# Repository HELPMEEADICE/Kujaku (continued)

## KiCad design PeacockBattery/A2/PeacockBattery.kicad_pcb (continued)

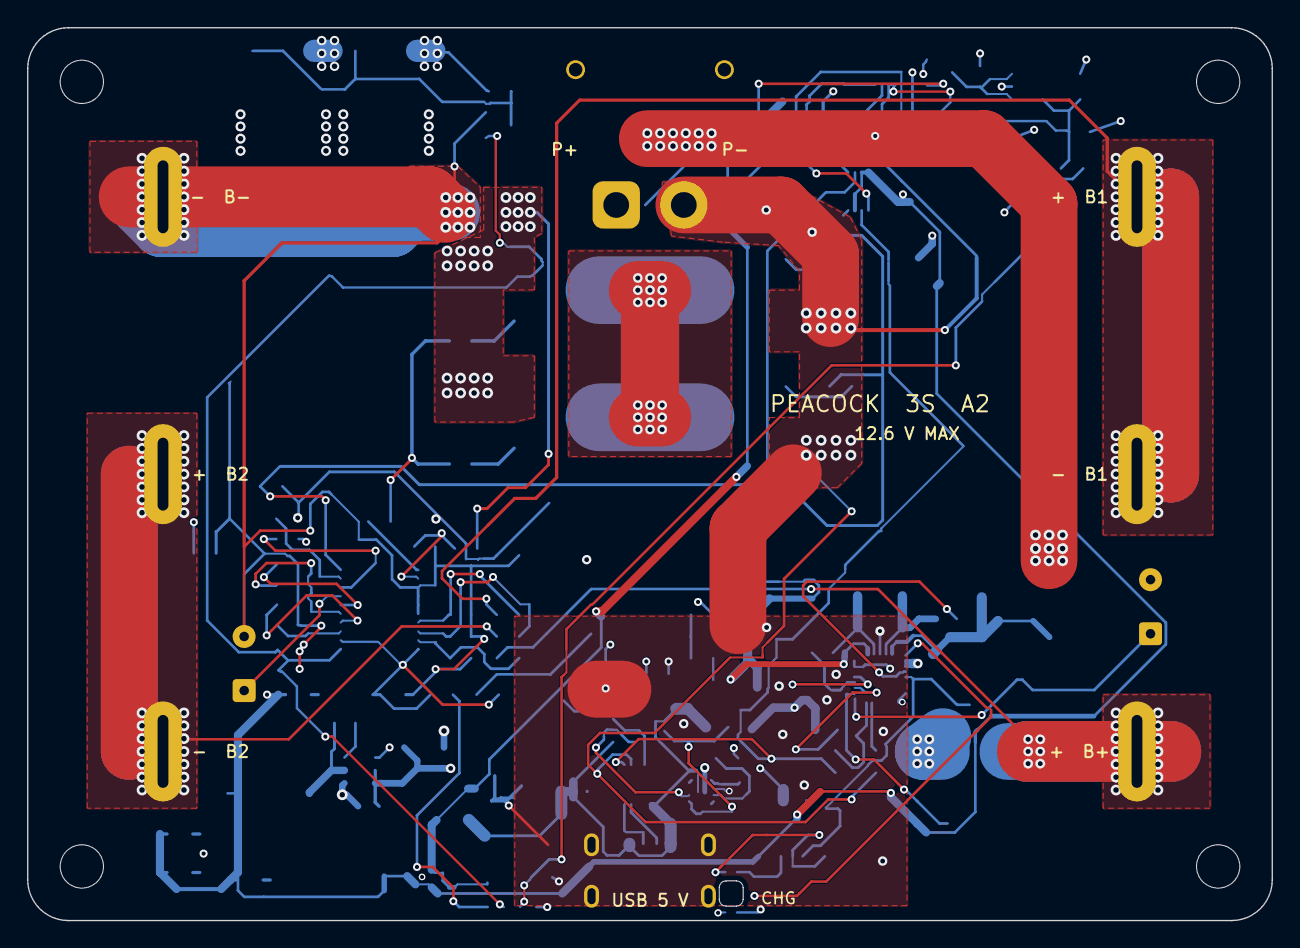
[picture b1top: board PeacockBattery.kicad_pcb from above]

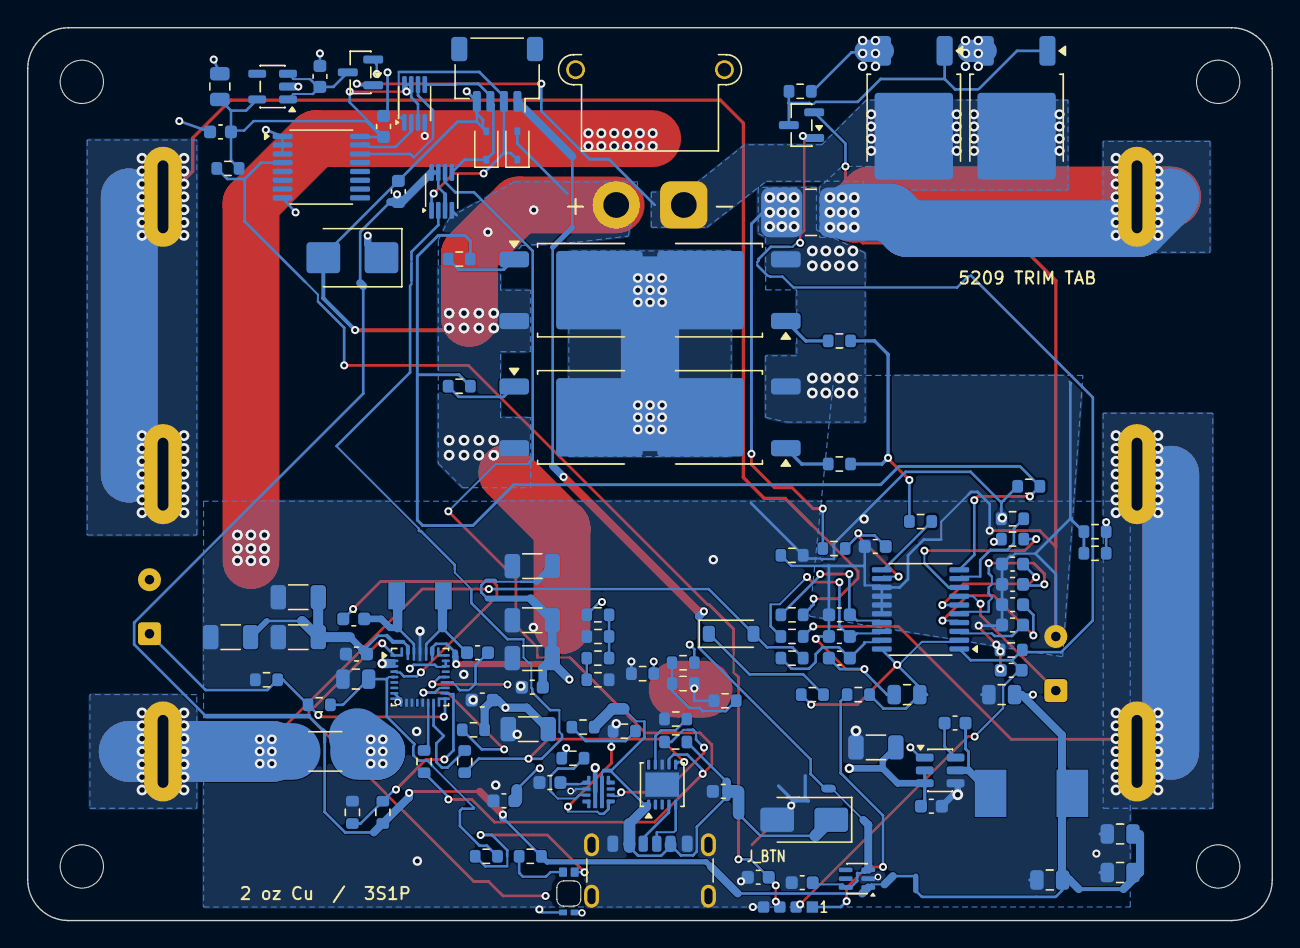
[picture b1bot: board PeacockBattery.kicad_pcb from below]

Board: 4 copper layers, 92.0 x 66.0 mm, 126 parts (116 on the bottom side), 75 nets.

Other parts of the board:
MH1, MH2, MH3, MH4: MountingHole_3.2mm_M3

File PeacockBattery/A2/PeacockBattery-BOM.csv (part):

位号,数量,规格,厂商,订购型号或规格,KiCad 封装,安装面,LCSC,SMT_Populate,JLCPCB 库别,装配说明
BT1,1,5209 trimmed,Keystone,TBD,PeacockBattery:Keystone_5209_Trimmed,F,,No,N/A,焊接前修剪原装长焊耳，装入镀通槽并完全坐靠后从 PCB 底面量取突出 ≤1.50 mm。名义肩下 2.80 ±0.10 mm。去毛刺并复核插入与焊脚。
BT2,1,5209 trimmed,Keystone,TBD,PeacockBattery:Keystone_5209_Trimmed,F,,No,N/A,焊接前修剪原装长焊耳，装入镀通槽并完全坐靠后从 PCB 底面量取突出 ≤1.50 mm。名义肩下 2.80 ±0.10 mm。去毛刺并复核插入与焊脚。
BT3,1,5209 trimmed,Keystone,TBD,PeacockBattery:Keystone_5209_Trimmed,F,,No,N/A,焊接前修剪原装长焊耳，装入镀通槽并完全坐靠后从 PCB 底面量取突出 ≤1.50 mm。名义肩下 2.80 ±0.10 mm。去毛刺并复核插入与焊脚。
BT4,1,5209 trimmed,Keystone,TBD,PeacockBattery:Keystone_5209_Trimmed,F,,No,N/A,焊接前修剪原装长焊耳，装入镀通槽并完全坐靠后从 PCB 底面量取突出 ≤1.50 mm。名义肩下 2.80 ±0.10 mm。去毛刺并复核插入与焊脚。
BT5,1,5209 trimmed,Keystone,TBD,PeacockBattery:Keystone_5209_Trimmed,F,,No,N/A,焊接前修剪原装长焊耳，装入镀通槽并完全坐靠后从 PCB 底面量取突出 ≤1.50 mm。名义肩下 2.80 ±0.10 mm。去毛刺并复核插入与焊脚。
BT6,1,5209 trimmed,Keystone,TBD,PeacockBattery:Keystone_5209_Trimmed,F,,No,N/A,焊接前修剪原装长焊耳，装入镀通槽并完全坐靠后从 PCB 底面量取突出 ≤1.50 mm。名义肩下 2.80 ±0.10 mm。去毛刺并复核插入与焊脚。
C1,1,100nF 50V,YAGEO,CC0603KRX7R9BB104,Capacitor_SMD:C_0603_1608Metric,B,C14663,Yes,Basic,X7R，±10%，未标耐压者用 ≥50 V，复核直流偏压
C2,1,100nF 50V,YAGEO,CC0603KRX7R9BB104,Capacitor_SMD:C_0603_1608Metric,B,C14663,Yes,Basic,X7R，±10%，未标耐压者用 ≥50 V，复核直流偏压
C3,1,100nF 50V,YAGEO,CC0603KRX7R9BB104,Capacitor_SMD:C_0603_1608Metric,B,C14663,Yes,Basic,X7R，±10%，未标耐压者用 ≥50 V，复核直流偏压
C4,1,10uF 25V,Samsung Electro Mechanics,CL21A106KAYNNNE,Capacitor_SMD:C_0805_2012Metric,B,C15850,Yes,Basic,BMS VCC 储能，10 µF / 25 V，0805。
C5,1,100nF 50V,YAGEO,CC0603KRX7R9BB104,Capacitor_SMD:C_0603_1608Metric,B,C14663,Yes,Basic,X7R，±10%，未标耐压者用 ≥50 V，复核直流偏压
C6,1,100nF 50V,YAGEO,CC0603KRX7R9BB104,Capacitor_SMD:C_0603_1608Metric,B,C14663,Yes,Basic,X7R，±10%，未标耐压者用 ≥50 V，复核直流偏压
C7,1,10nF 50V,FH Guangdong Fenghua Advanced Tech,0603B103K500NT,Capacitor_SMD:C_0603_1608Metric,B,C57112,Yes,Basic,过流定时，保持 10 nF / 50 V。
C8,1,10nF 50V,FH Guangdong Fenghua Advanced Tech,0603B103K500NT,Capacitor_SMD:C_0603_1608Metric,B,C57112,Yes,Basic,过流定时，保持 10 nF / 50 V。
C9,1,10nF 50V,FH Guangdong Fenghua Advanced Tech,0603B103K500NT,Capacitor_SMD:C_0603_1608Metric,B,C57112,Yes,Basic,分流检测滤波，保持 10 nF / 50 V。
C10,1,1uF 50V,Samsung Electro Mechanics,CL10A105KB8NNNC,Capacitor_SMD:C_0603_1608Metric,B,C15849,Yes,Basic,陶瓷 X7R 或 X5R。按偏压下有效容量、纹波电流和公差选型。
C11,1,4.7nF 50V,FH Guangdong Fenghua Advanced Tech,0603B472K500NT,Capacitor_SMD:C_0603_1608Metric,B,C53987,Yes,Basic,电子保险丝 dV/dt 电容，保持 4.7 nF。
C12,1,1uF 50V,Samsung Electro Mechanics,CL10A105KB8NNNC,Capacitor_SMD:C_0603_1608Metric,B,C15849,Yes,Basic,陶瓷 X7R 或 X5R。按偏压下有效容量、纹波电流和公差选型。
C13,1,4.7uF 25V,Samsung Electro Mechanics,CL21A475KAQNNNE,Capacitor_SMD:C_0805_2012Metric,B,C1779,Yes,Basic,REGN 去耦，4.7 µF / 25 V。
C14,1,100nF 50V,YAGEO,CC0603KRX7R9BB104,Capacitor_SMD:C_0603_1608Metric,B,C14663,Yes,Basic,陶瓷 X7R 或 X5R。按偏压下有效容量、纹波电流和公差选型。
C15,1,100nF 50V,YAGEO,CC0603KRX7R9BB104,Capacitor_SMD:C_0603_1608Metric,B,C14663,Yes,Basic,陶瓷 X7R 或 X5R。按偏压下有效容量、纹波电流和公差选型。
C16,1,10uF 50V,Samsung Electro Mechanics,CL31A106KBHNNNE,Capacitor_SMD:C_1206_3216Metric,B,C13585,Yes,Basic,10 µF / 50 V、1206，保留受偏压下的容量余量。
C17,1,10uF 50V,Samsung Electro Mechanics,CL31A106KBHNNNE,Capacitor_SMD:C_1206_3216Metric,B,C13585,Yes,Basic,10 µF / 50 V、1206，保留受偏压下的容量余量。
C18,1,10uF 50V,Samsung Electro Mechanics,CL31A106KBHNNNE,Capacitor_SMD:C_1206_3216Metric,B,C13585,Yes,Basic,10 µF / 50 V、1206，保留受偏压下的容量余量。
C19,1,100nF 50V,YAGEO,CC0603KRX7R9BB104,Capacitor_SMD:C_0603_1608Metric,B,C14663,Yes,Basic,陶瓷 X7R 或 X5R。按偏压下有效容量、纹波电流和公差选型。
C20,1,22uF 25V,Samsung Electro Mechanics,CL31A226KAHNNNE,Capacitor_SMD:C_1206_3216Metric,B,C12891,Yes,Basic,22 µF / 25 V、1206，保留充电 SYS 在偏压下的容量余量。
C21,1,22uF 25V,Samsung Electro Mechanics,CL31A226KAHNNNE,Capacitor_SMD:C_1206_3216Metric,B,C12891,Yes,Basic,22 µF / 25 V、1206，保留充电 SYS 在偏压下的容量余量。
C22,1,22uF 25V,Samsung Electro Mechanics,CL31A226KAHNNNE,Capacitor_SMD:C_1206_3216Metric,B,C12891,Yes,Basic,22 µF / 25 V、1206，保留充电 SYS 在偏压下的容量余量。
C23,1,100nF 50V,YAGEO,CC0603KRX7R9BB104,Capacitor_SMD:C_0603_1608Metric,B,C14663,Yes,Basic,陶瓷 X7R 或 X5R。按偏压下有效容量、纹波电流和公差选型。
C24,1,10uF 50V,Samsung Electro Mechanics,CL31A106KBHNNNE,Capacitor_SMD:C_1206_3216Metric,B,C13585,Yes,Basic,10 µF / 50 V、1206，保留受偏压下的容量余量。
C25,1,100nF 50V,YAGEO,CC0603KRX7R9BB104,Capacitor_SMD:C_0603_1608Metric,B,C14663,Yes,Basic,陶瓷 X7R 或 X5R。按偏压下有效容量、纹波电流和公差选型。
C26,1,10uF 50V,Samsung Electro Mechanics,CL31A106KBHNNNE,Capacitor_SMD:C_1206_3216Metric,B,C13585,Yes,Basic,AP63205 输入储能，50 V 器件，临近 VIN。
C27,1,100nF 50V,YAGEO,CC0603KRX7R9BB104,Capacitor_SMD:C_0603_1608Metric,B,C14663,Yes,Basic,AP63205 VIN 与 GND 的近端高频旁路。
C29,1,100nF 50V,YAGEO,CC0603KRX7R9BB104,Capacitor_SMD:C_0603_1608Metric,B,C14663,Yes,Basic,陶瓷 X7R 或 X5R。按偏压下有效容量、纹波电流和公差选型。
C30,1,22uF 25V,Samsung Electro Mechanics,CL21A226MAQNNNE,Capacitor_SMD:C_0805_2012Metric,B,C45783,Yes,Basic,22 µF / 25 V、0805，WAKE_5V 输出电容。
C31,1,22uF 25V,Samsung Electro Mechanics,CL21A226MAQNNNE,Capacitor_SMD:C_0805_2012Metric,B,C45783,Yes,Basic,22 µF / 25 V、0805，WAKE_5V 输出电容。
C32,1,22uF 25V,Samsung Electro Mechanics,CL21A226MAQNNNE,Capacitor_SMD:C_0805_2012Metric,B,C45783,Yes,Basic,22 µF / 25 V、0805，WAKE_5V 输出电容。
C33,1,22uF 25V,Samsung Electro Mechanics,CL21A226MAQNNNE,Capacitor_SMD:C_0805_2012Metric,B,C45783,Yes,Basic,22 µF / 25 V、0805，WAKE_5V 输出电容。
C34,1,1uF 50V,Samsung Electro Mechanics,CL10A105KB8NNNC,Capacitor_SMD:C_0603_1608Metric,B,C15849,Yes,Basic,陶瓷 X7R 或 X5R。按偏压下有效容量、纹波电流和公差选型。
C35,1,100nF 50V,YAGEO,CC0603KRX7R9BB104,Capacitor_SMD:C_0603_1608Metric,B,C14663,Yes,Basic,陶瓷 X7R 或 X5R。按偏压下有效容量、纹波电流和公差选型。
C36,1,100nF 50V,YAGEO,CC0603KRX7R9BB104,Capacitor_SMD:C_0603_1608Metric,B,C14663,Yes,Basic,
C37,1,100nF 50V,YAGEO,CC0603KRX7R9BB104,Capacitor_SMD:C_0603_1608Metric,B,C14663,Yes,Basic,
C38,1,1uF 50V,Samsung,CL10A105KB8NNNC,Capacitor_SMD:C_0603_1608Metric,B,C15849,Yes,Basic,
C39,1,10uF 25V,Samsung,CL21A106KAYNNNE,Capacitor_SMD:C_0805_2012Metric,B,C15850,Yes,Basic,
C40,1,100nF 50V,YAGEO,CC0603KRX7R9BB104,Capacitor_SMD:C_0603_1608Metric,B,C14663,Yes,Basic,
C41,1,100nF 50V,YAGEO,CC0603KRX7R9BB104,Capacitor_SMD:C_0603_1608Metric,B,C14663,Yes,Basic,
CELL,3,Ø18.50 × 66.50–68.00 mm 凸口 18650,待选,同型号、同批次动力电芯,可拆卸,F,,No,N/A,整组一致性及 15 A 稳态和 20 A 脉冲额定按最终电芯验收。
D1,1,1N4148W,ST Semtech,1N4148W,Diode_SMD:D_SOD-123,B,C81598,Yes,Basic,基础库低漏电高速二极管，SOD-123，1 为阴极。
D2,1,SMBJ15A,hongjiacheng,SMBJ15A,Diode_SMD:D_SMB,B,C19077569,Yes,Preferred Extended,15 V 单向 TVS，SMB，1 为阴极。
D3,1,SMAJ20A,hongjiacheng,SMAJ20A,Diode_SMD:D_SMA,B,C41376408,Yes,Preferred Extended,20 V 单向 TVS，SMA，1 为阴极。热插拔峰值以带线实测为准。
D4,1,23-22B/R7G6C-A30/2T,Everlight Elec,23-22B/R7G6C-A30/2T,PeacockBattery:LED_Everlight_23-22B_Reverse,B,C424084,Yes,Extended,"B 面反向出光，光轴居中于 (52.00, 2.00) mm。1=绿阳，2=绿阴，3=红阳，4=红阴。"
D5,1,PESD3V3U1UA,Nexperia,"PESD3V3U1UA,115",Diode_SMD:D_SOD-323,B,C403915,Yes,Extended,SDA 对地 ESD，1 为阴极。
D6,1,PESD3V3U1UA,Nexperia,"PESD3V3U1UA,115",Diode_SMD:D_SOD-323,B,C403915,Yes,Extended,SCL 对地 ESD，1 为阴极。
D7,1,BAT54C,Jiangsu Changjing Electronics,BAT54C,Package_TO_SOT_SMD:SOT-23,B,C2135,Yes,Extended,XT30_SW 与 WAKE_5V 合路，共阴极。
F1,1,20A / 65V,Littelfuse,0451020.MRL,Fuse:Fuse_Littelfuse-NANO2-451_453,B,C178980,Yes,Extended,20 A 快断保险丝，按装壳温度复核降额
J1,1,USB4125-GF-A,Global Connector Technology,USB4125-GF-A,PeacockBattery:USB4125_HandAssembly,B,C3151650,No,Extended,B 面手焊。不下钢网。六触点双 CC，保留插口中心及 0.80 mm 外伸。
J2,1,XT30PW-M30.G.Y,Changzhou Amass Elec,XT30PW-M30.G.Y,PeacockBattery:XT30PW-M_Edge,B,C431092,No,Extended,B 面手焊。保留 5.00 mm 脚距及原固定孔，1=P+，2=P−。
J3,1,10k BMS sensor,通用,"10k NTC, insulated leads",Connector_Wire:SolderWire-0.15sqmm_1x02_P4mm_D0.5mm_OD1.5mm,B,,No,N/A,需另装电芯贴附式 10 kΩ NTC，温度动作点需标定
J4,1,103AT-2,SEMITEC,103AT-2,Connector_Wire:SolderWire-0.15sqmm_1x02_P4mm_D0.5mm_OD1.5mm,B,,No,N/A,外置绝缘贴附 NTC，10 kΩ / 3435 K，核对接头极性与引脚底面净空。
J5,1,SM04B-SRSS-TB(LF)(SN),JST,SM04B-SRSS-TB(LF)(SN),PeacockBattery:JST_SH_SM04B_HandAssembly,B,C160404,No,Extended,B 面手焊。不下钢网。1=CHG_5V，2=SDA，3=SCL，4=GND。
J6,1,J_BTN,Hand assembly,Wire-to-pad,PeacockBattery:Grip_1x04_SolderPads,B,N/A,No,N/A,J_BTN，四路手焊，B 面无锡膏。红 1、黑 2、黄 3、绿 4。
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
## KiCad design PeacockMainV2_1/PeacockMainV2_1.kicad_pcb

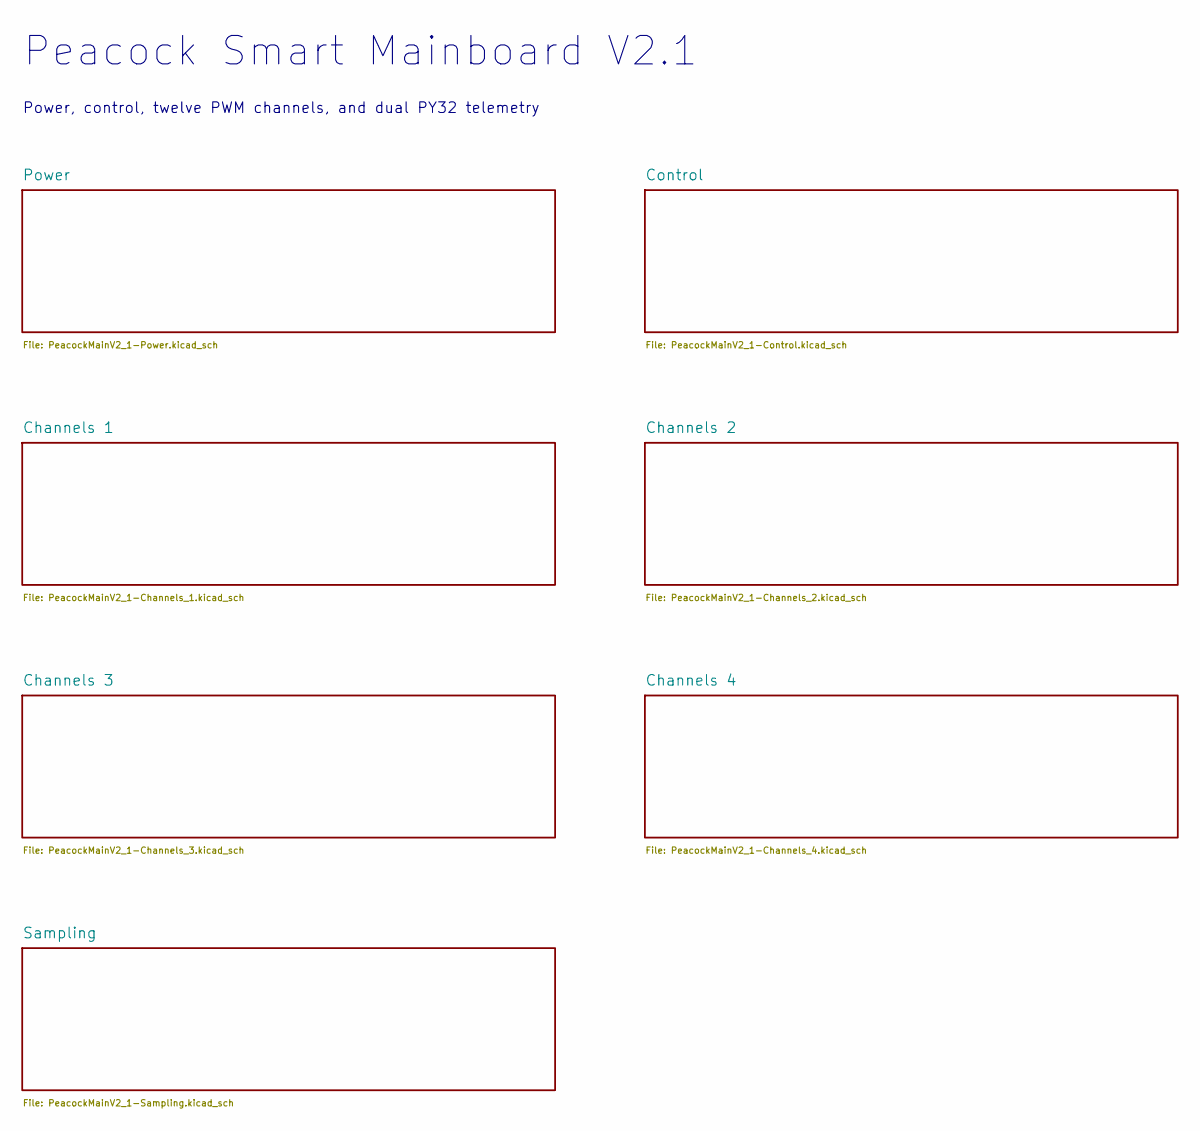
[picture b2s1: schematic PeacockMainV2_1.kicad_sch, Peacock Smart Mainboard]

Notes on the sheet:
Peacock Smart Mainboard V2.1
Power, control, twelve PWM channels, and dual PY32 telemetry

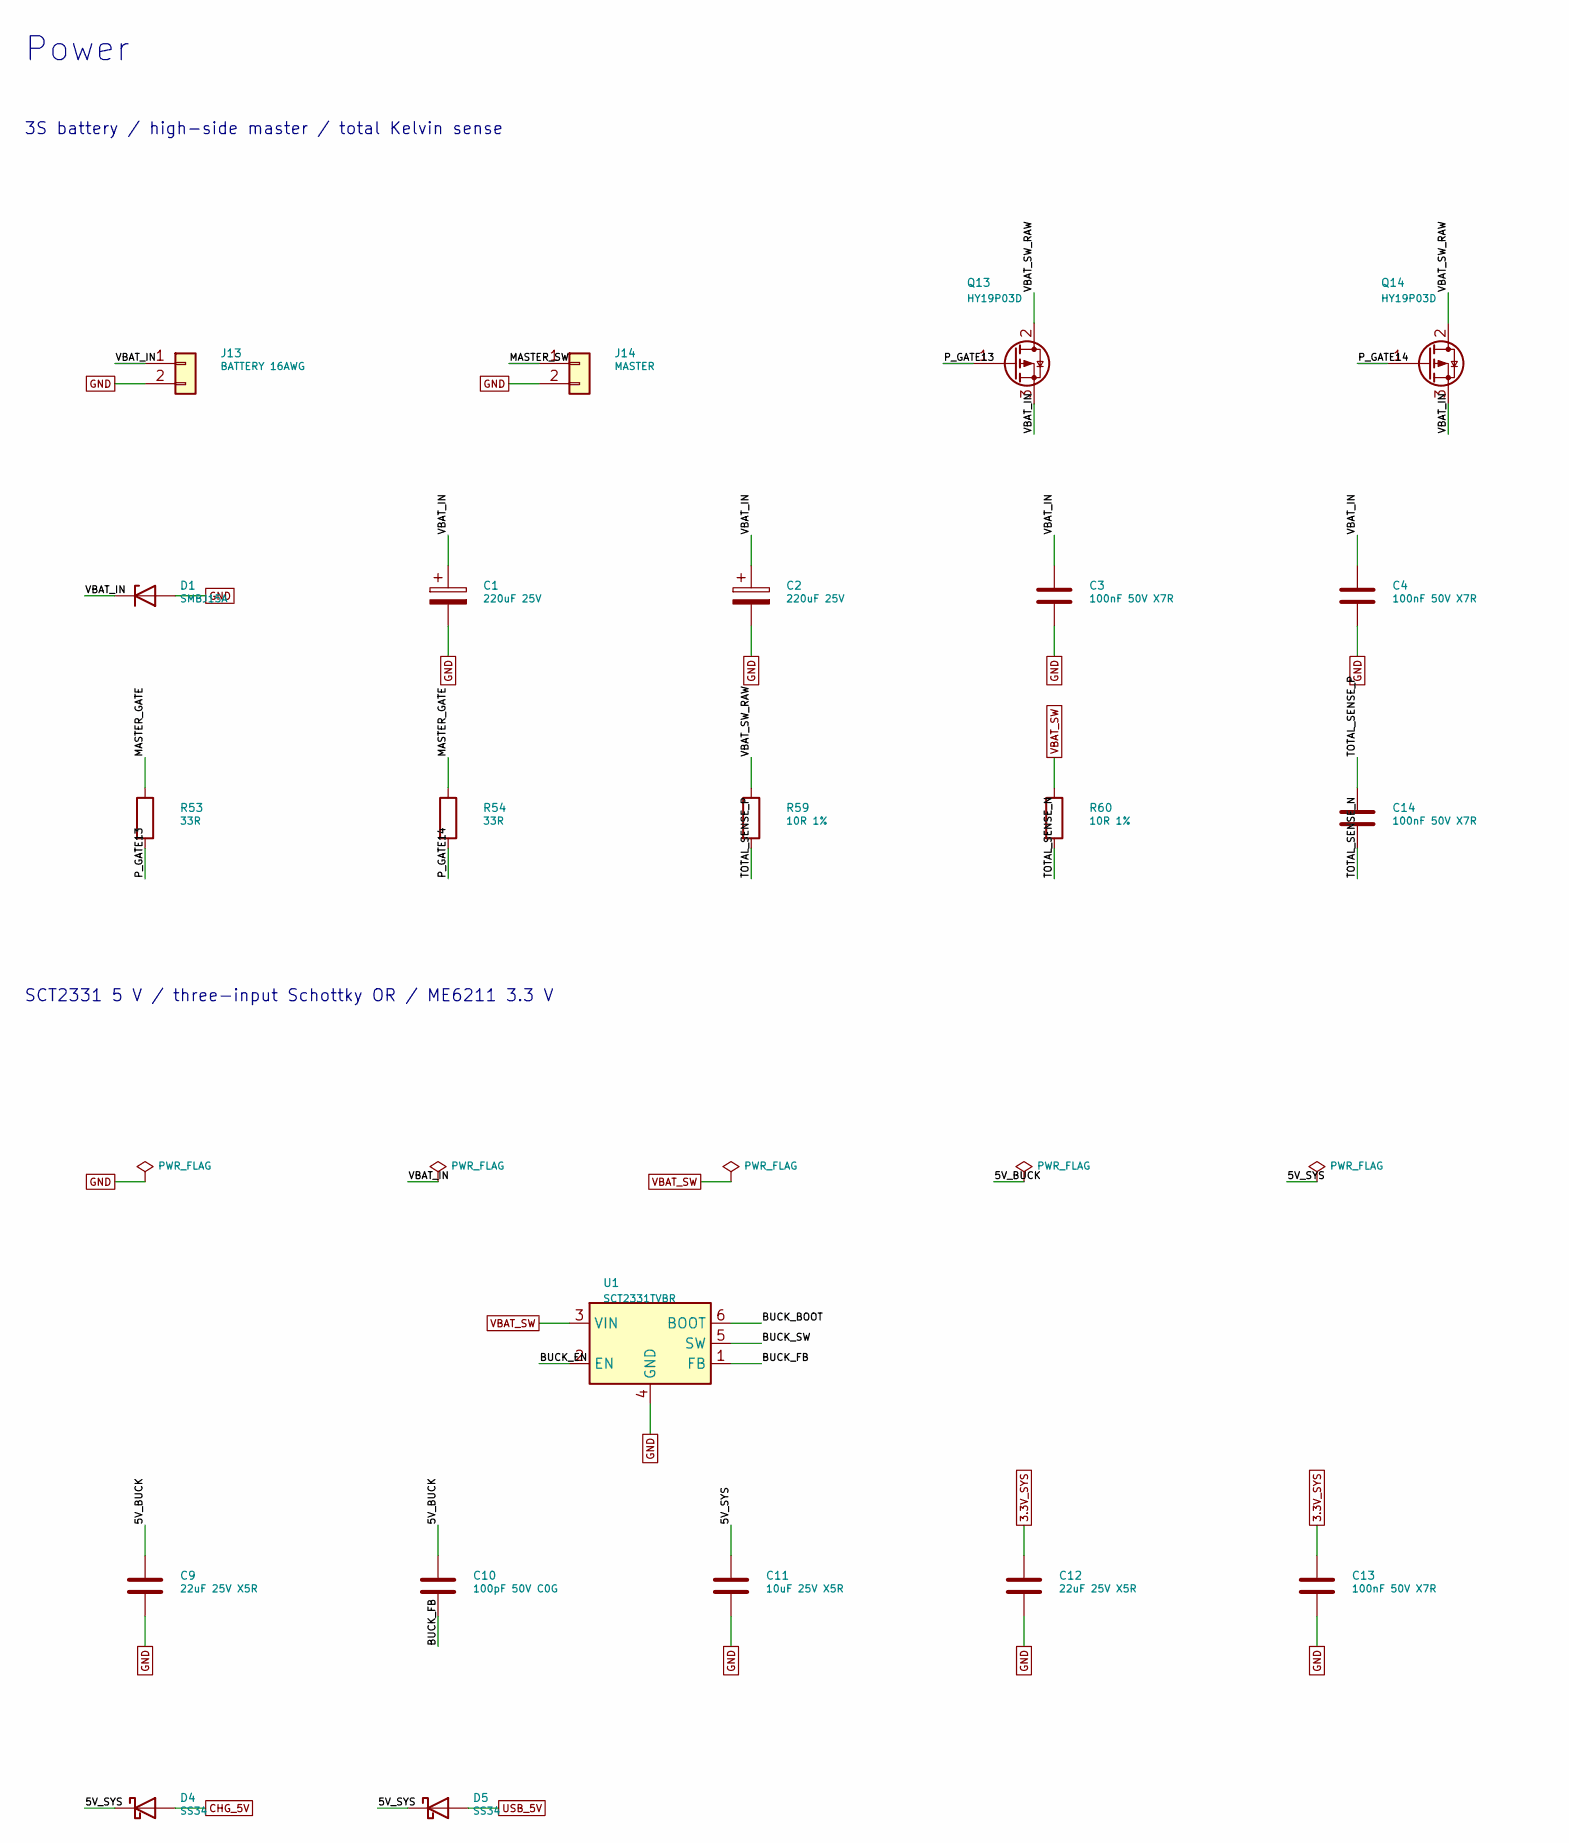
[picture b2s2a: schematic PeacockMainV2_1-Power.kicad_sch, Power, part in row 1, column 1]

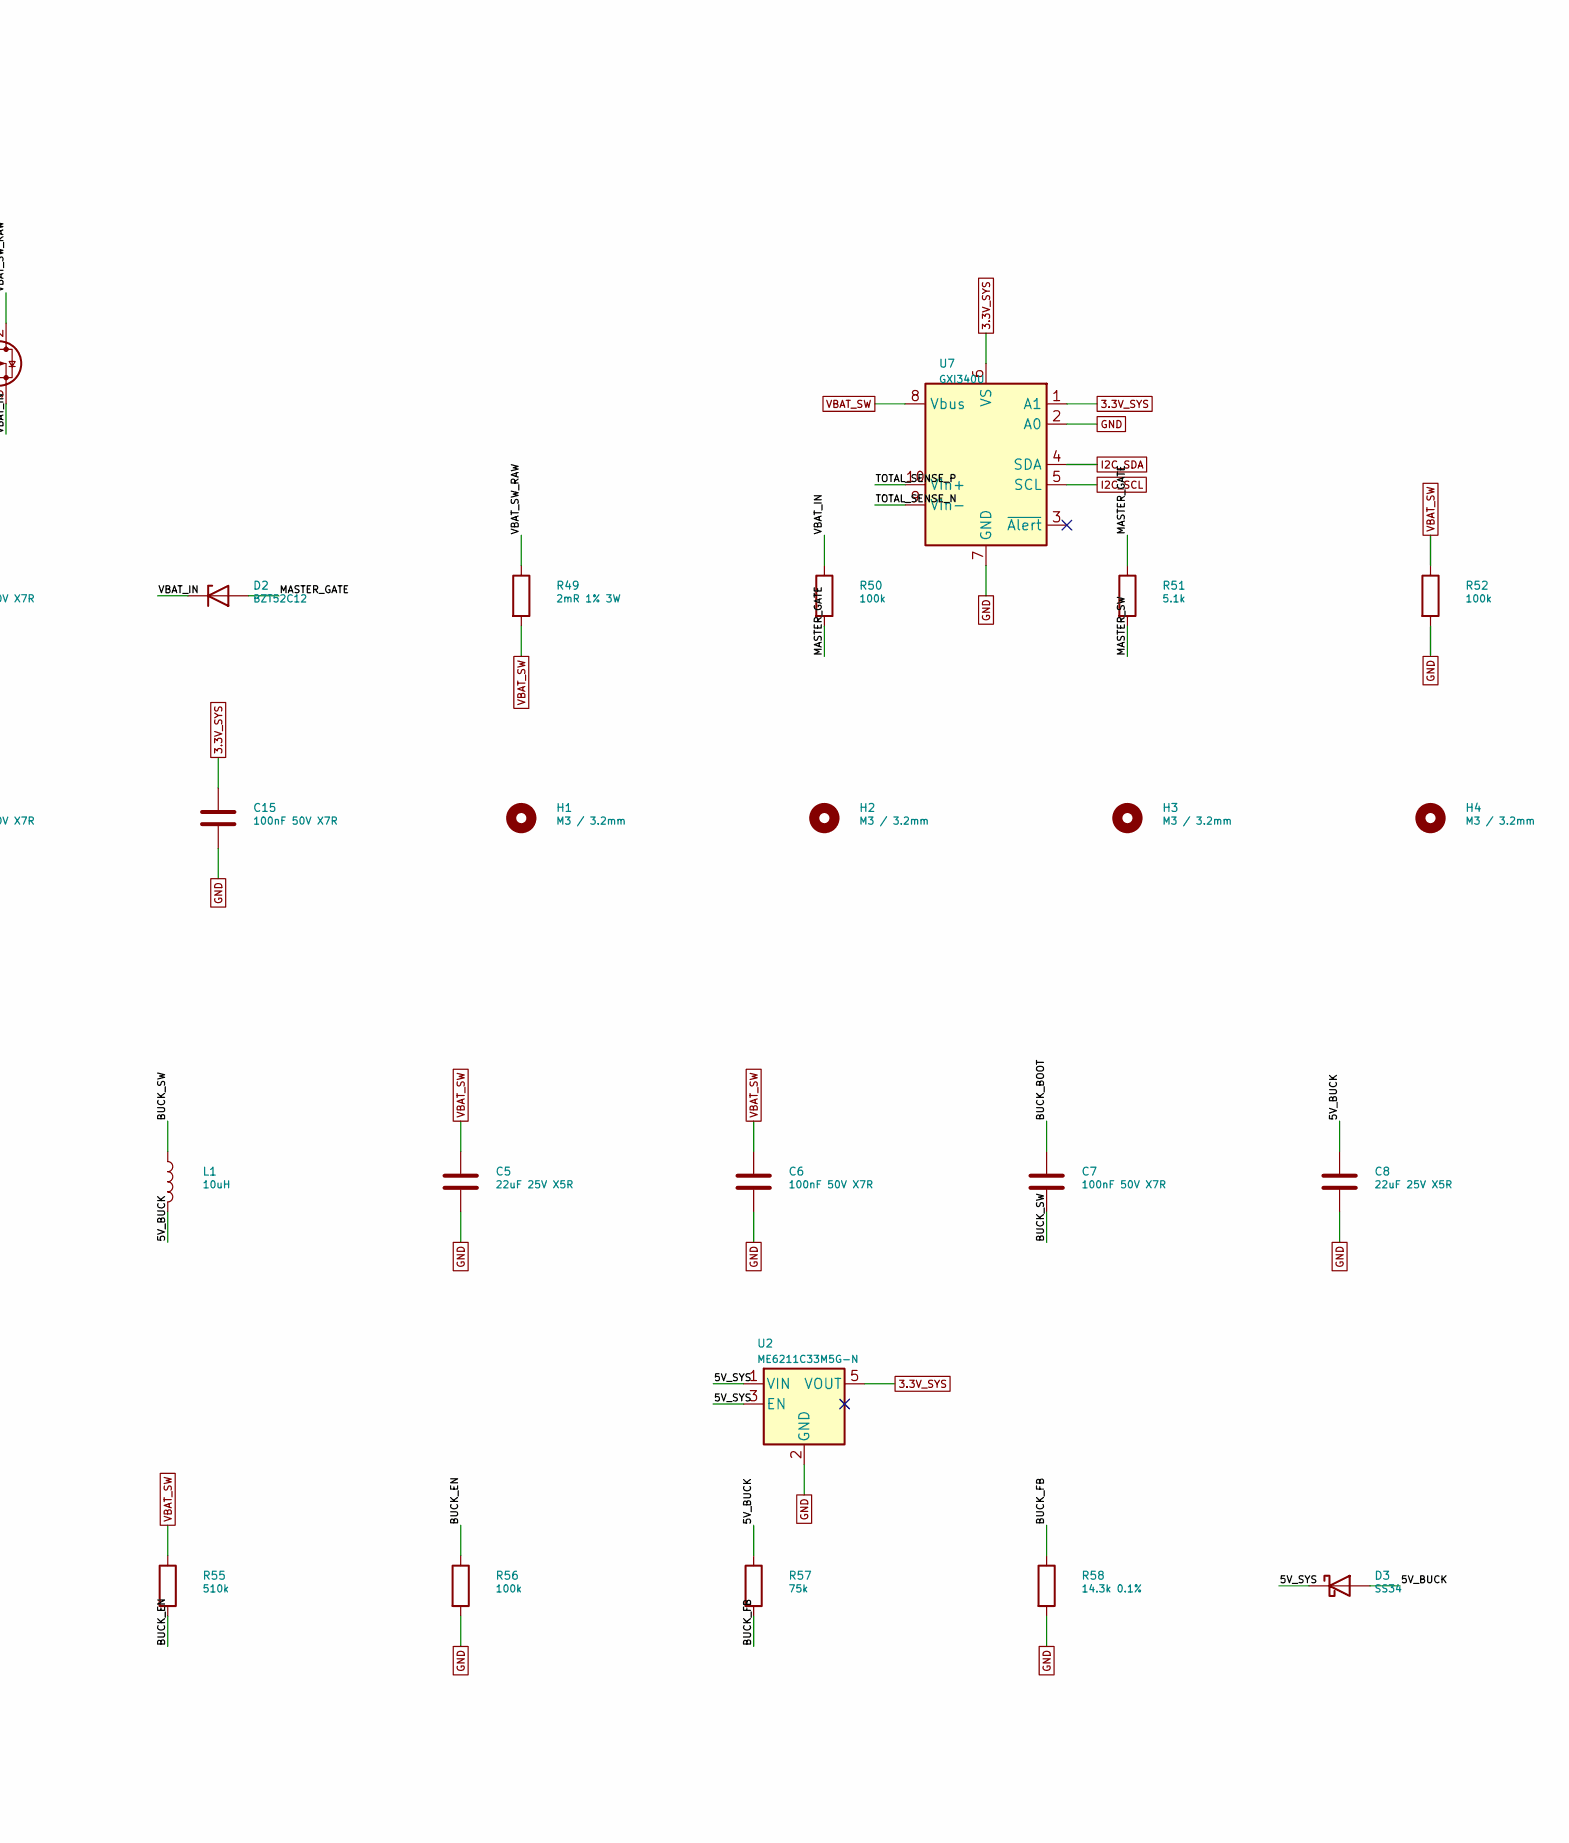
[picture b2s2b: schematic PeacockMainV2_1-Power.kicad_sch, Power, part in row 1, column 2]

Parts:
C1, C2: 220uF 25V; Cap_8x10p5; MPN EEH-ZA1E221P
C3, C4, C6, C7, C13, C14: 100nF 50V X7R; C_0603_1608Metric; MPN CC0603KRX7R9BB104; LCSC C14663
C5: 22uF 25V X5R; C_1206_3216Metric; MPN CL31A226KAHNNNE; LCSC C12891
C8, C9, C12: 22uF 25V X5R; C_0805_2012Metric; MPN CL21A226MAQNNNE; LCSC C45783
C10: 100pF 50V C0G; C_0603_1608Metric; MPN CL10C101JB8NNNC; LCSC C14858
C11: 10uF 25V X5R; C_0805_2012Metric; MPN CL21A106KAYNNNE; LCSC C15850
C15: 100nF 50V X7R; C_0402_1005Metric; MPN CL05B104KB54PNC; LCSC C307331
D1: SMBJ15A; D_SMB; MPN SMBJ15A; LCSC C19077569
D2: BZT52C12; D_SOD-123; MPN BZT52C12; LCSC C19077410
D3, D4, D5: SS34; D_SMA; MPN SS34; LCSC C8678
H1, H2, H3, H4: M3 / 3.2mm; MountingHole_3.2mm_M3
J13: BATTERY 16AWG; Battery_16AWG
J14: MASTER; Remote_Switch
L1: 10uH; L_Coilcraft_XAL6060-XXX; MPN YSPIT0660A-100M; LCSC C18199451
Q13, Q14: HY19P03D; TO-252-2; MPN HY19P03D; LCSC C122492
R49: 2mR 1% 3W; R_2512_6332Metric; MPN HoLLR2512-3W-2mR-1%; LCSC C2994640
R50, R52, R56: 100k; R_0603_1608Metric; MPN 0603WAF1003T5E; LCSC C25803
R51: 5.1k; R_0603_1608Metric; MPN 0603WAF5101T5E; LCSC C23186
R53, R54: 33R; R_0603_1608Metric; MPN 0603WAF330JT5E; LCSC C23140
R55: 510k; R_0603_1608Metric; MPN 0603WAF5103T5E; LCSC C23192
R57: 75k; R_0603_1608Metric; MPN 0603WAF7502T5E; LCSC C23242
R58: 14.3k 0.1%; R_0603_1608Metric; MPN RT0603BRE0714K3L; LCSC C705810
R59: 10R 1%; R_0402_1005Metric; MPN 0402WGF100JTCE; LCSC C25077
R60: 10R 1%; R_0603_1608Metric; MPN 0603WAF100JT5E; LCSC C22859
U1: SCT2331TVBR; SOT-23-6; MPN SCT2331TVBR; LCSC C509068
U2: ME6211C33M5G-N; SOT-23-5; MPN ME6211C33M5G-N; LCSC C82942
U7: GXI340U; MSOP-10_3x3mm_P0.50mm_HandAssembly; MPN GXI340U

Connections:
3.3V_SYS: C12.1, C13.1, C15.1, U2.5 (VOUT), U7.1 (A1), U7.6 (VS); also elsewhere on the board
/Power/5V_BUCK: C8.1, C9.1, C10.1, D3.2 (A), L1.2, R57.1
/Power/5V_SYS: C11.1, D3.1 (K), D4.1 (K), D5.1 (K), U2.1 (VIN), U2.3 (EN)
/Power/BUCK_BOOT: C7.1, U1.6 (BOOT)
/Power/BUCK_EN: R55.2, R56.1, U1.2 (EN)
/Power/BUCK_FB: C10.2, R57.2, R58.1, U1.1 (FB)
/Power/BUCK_SW: C7.2, L1.1, U1.5 (SW)
/Power/MASTER_GATE: D2.2 (A), R50.2, R51.1, R53.1, R54.1
/Power/MASTER_SW: J14.1, R51.2
/Power/P_GATE13: Q13.1 (G), R53.2
/Power/P_GATE14: Q14.1 (G), R54.2
/Power/TOTAL_SENSE_N: C14.2, R60.2, U7.9 (Vin-)
/Power/TOTAL_SENSE_P: C14.1, R59.2, U7.10 (Vin+)
/Power/VBAT_IN: C1.1, C2.1, C3.1, C4.1, D1.1 (K), D2.1 (K), J13.1, Q13.3 (S), Q14.3 (S), R50.1
/Power/VBAT_SW_RAW: Q13.2 (D), Q14.2 (D), R49.1, R59.1
CHG_5V: D4.2 (A); also elsewhere on the board
GND: C1.2, C2.2, C3.2, C4.2, C5.2, C6.2, C8.2, C9.2, C11.2, C12.2, C13.2, C15.2, D1.2 (A), J13.2, J14.2, R52.2, R56.2, R58.2, U1.4 (GND), U2.2 (GND), U7.2 (A0), U7.7 (GND); also elsewhere on the board
I2C_SCL: U7.5 (SCL); also elsewhere on the board
I2C_SDA: U7.4 (SDA); also elsewhere on the board
USB_5V: D5.2 (A); also elsewhere on the board
VBAT_SW: C5.1, C6.1, R49.2, R52.1, R55.1, R60.1, U1.3 (VIN), U7.8 (Vbus); also elsewhere on the board

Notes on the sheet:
Power
3S battery / high-side master / total Kelvin sense
SCT2331 5 V / three-input Schottky OR / ME6211 3.3 V
